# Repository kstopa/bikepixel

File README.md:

# Bike Pixels

Open Source Hardware project to build a set of highly customizable bycicle lights based on Arduino and Neo Pixel RGB matrixes. Currently all models can present different images in different colors with custom effects (blinking, bitting) and with adjustable brightness.

Check [Bike Pixel Official site](https://bikepixels.com) to the more details and recent news.

## Required software
All required applications to edit and design the different Bike Pixel models are open source. Bellow you can find all the tools that were used to design Bike Pixels:

* [Arduino IDE](https://www.arduino.cc/en/Main/Software): to write, biuld and upload the code to the Arduino board.
* [FreeCAD](https://www.freecadweb.org/wiki/Download): to design the cases.
* [KiCAD](http://kicad.org/download/): to design electronic schemas and the PCBs.
* [Fritzing](https://fritzing.org): only for circuit sketch documentation.

## Bike Pixel L (or rear)

This model it is intended to be installed in the back part of the bike like the saddle or over bike structure. Main properties and parts:

* Preset 10 diferent icons
* Adjustable color and brightness
* 64 LEDs NeoPixel matrix
* 84 x 84 x 14 mm (3.3 x 3.3 x 0.55 in)

### Components

To build your own Bike Pixel L you should have all the elements listed on this bill of materials:

* 1 x Arduino Pro Mini or Nano;
* 1 x NeoPixel 8x8 matrix (80x80x2mm);
* 3 x 10 kΩ resistence;
* 1 x 470 Ω resistence;
* 2 x 22 kΩ resistor;
* 1 x 1000 uf/6.3V capacitator (recommended but optional);
* 3 x vertical touch switches;
* 1 x on\off botton (optional if your battery holder have one built-in);
* 1 x TP4056 module;
* 1 x 5V Step-up module;
* 1 x >2000 mAh LiPo battery;
* 1 x M3 30mm bolt;
* 1 x M3 20mm bolt; 
* 2 x M3 nuts;
* connection PCB;
* wires and soldering stuff;
* 3D printed case;
* 3D printed holder.

More details on each part are commented on following points. Links to different proviedars and prices can be found on this blog entry.

### Case

The case is divided in multiple parts designed to be 3D printed. Current designs include body and holder models.

#### Main body

The body is composed the main body and a cover. You can print them using PLA altought for the cover a 1 mm thick piece of plexi is recommended.

You can get production files bellow.

| Part |                       Files                        |  
|------|----------------------------------------------------|
| Body | [sld](rear/case/body/case_bikepixels_rear.stl)     |
| Cover| [sld](rear/case/cover/case_bikepixels_rear_cover.stl), [svg](rear/case/cover/case_bikepixels_rear_cover.svg), [pdf](rear/case/cover/case_bikepixels_rear_cover.pdf) |

#### Bike attachment 

Current holder design is divided into two pieces. An attachment and a hook. To mount them on a bycicle you will need 2 x M3 nuts and 2 x M3 bolts of 30 and 20mm in lenght.

You can get production files bellow.

|  Part      |                           Files                             |
|------------|-------------------------------------------------------------|
| Hook       | [sld](rear/case/holder/holder_base_28mm-holder_hook.stl)    |
| Attachment | [sld](rear/case/holder/holder_base_28mm-holder_attach.stl)  |

### Electronics

#### Main components

To build your L model you will need all the electronic parts listed bellow along with some additional requirements.

|            Part              |              Comment                   |
|------------------------------|----------------------------------------|
| Arduino Nano or Pro Mini     | Clone or original                      |
| USB C TP4056 charging module | More information on [this blog entry](https://bikepixels.com/2019/11/10/how-to-add-a-lipo-battery-in-our-arduino-projects/)   |
| 5V Step-up module            | Any module designed for LiPo batteries |
| NeoPixel 8x8 RGB matrix      | Flexible 80x80x2mm model               |
| >2000 LiPo battery           | Max. 4 mm thicknes                     |

#### Conexions PCB

The PCB encapsulates the switches and manage connections between the Arduino board, the step-up module and the RGB matrix. All the design have been created with KiCAD. All the source files including schematinc, netlist and PCB board are availble [here](./rear/electronics/bikepixel rear/).

Production files are available in different formats and are linked bellow:

|                         Format                           |
|----------------------------------------------------------|
| [gerber](rear/electronics/production files/gerber)       |
| [pdf](rear/electronics/production files/pdf)             |
| [svg](rear/electronics/production files/svg)             |

#### Assambley

To connect evrything together please follow schema bellow. After soldering everthing you can proceed to upload the code to Arduino.

## Code 

To compile the BikePixel [code for Arduino](./rear/src/bikepixel_sketch.ino), you'll need some extra libraries:

* [Adafruit GFX](https://github.com/adafruit/Adafruit-GFX-Library)
* [Adafruit NeoPixel](https://github.com/adafruit/Adafruit_NeoPixel)
* [Adafruit NeoMatrix](https://github.com/adafruit/Adafruit_NeoMatrix)

Note that you can install these libraries directly from Arduino Studio (Sketch menu, > Include Library > Manage Libraries) or by placing it after download into the Arduino Library folder (usally in your home).

## Certification

Bike Pixel is certified by the Open Source Hardware Association ([OSHWA](https://oshwa.org)). 
OSWHA is a non-profit organization that advocates for open-source hardware focusing on promotion, education and commercialization of open 
products. OSHWA also manages certification program for open-source hardware that indicate that given product meet standard criteria for 
open-source compliance. Current Bike Pixel version has certificate number [PL000007](https://certification.oshwa.org/pl000007.html).

## License

As the project is compond by software, hardware and documentation each of these parts are licensed under the terms of specific license.

### Software License

Copyright © 2021 by BikePixels.com and contributors:

* Krzysztof Stopa ([kstopa](https://github.com/kstopa/)).

Bike Pixels contains free software: you can redistribute it and/or modify it under the terms of the GNU General Public License as published by the Free Software Foundation, either version 3 of the License, or any later version.

Bike Pixels is distributed in the hope that it will be useful, but WITHOUT ANY WARRANTY; without even the implied warranty of MERCHANTABILITY or FITNESS FOR A PARTICULAR PURPOSE. See the GNU Lesser General Public License for more details.

You should have received a copy of the GNU Lesser General Public License along with CAMS tools. If not, see http://www.gnu.org/licenses/.

### Hardware License

Copyright © 2021 by BikePixels.com and contributors:

* Krzysztof Stopa ([kstopa](https://github.com/kstopa/)).

Hardware elements is licensed under the CERN OHL v. 1.2.

You may redistribute and modify this documentation under the terms of the CERN OHL v.1.2. (http://ohwr.org/cernohl). This documentation is distributed WITHOUT ANY EXPRESS OR IMPLIED WARRANTY, INCLUDING OF MERCHANTABILITY, SATISFACTORY QUALITY AND FITNESS FOR A PARTICULAR PURPOSE. Please see the CERN OHL v.1.2 for applicable conditions.

### Documentation and images License

Copyright © 2021 by BikePixels.com and contributors:

* Krzysztof Stopa ([kstopa](https://github.com/kstopa/)).

Documentation and image files are distributed under the Attribution-NonCommercial-ShareAlike 4.0 International (CC BY-NC-SA 4.0) lisence. The full text of the license can be found at the [CC BY-NC-SA 4.0 page](https://creativecommons.org/licenses/by-nc-sa/4.0/legalcode).

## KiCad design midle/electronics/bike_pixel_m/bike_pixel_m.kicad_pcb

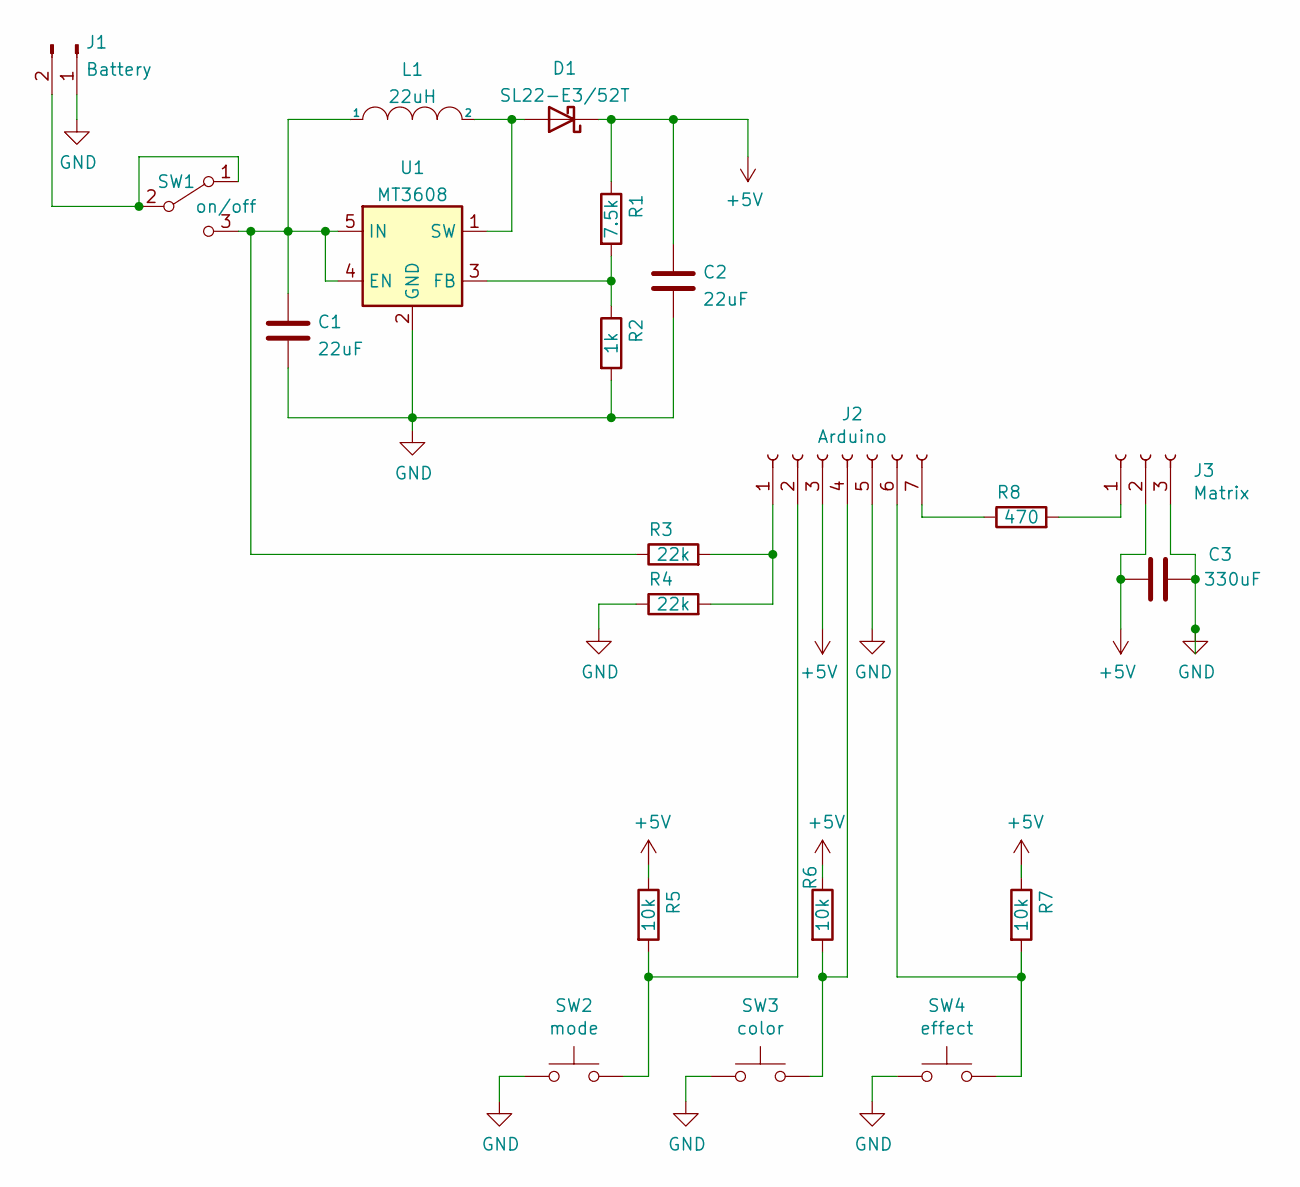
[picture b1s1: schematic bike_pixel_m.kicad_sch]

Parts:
C1, C2: 22uF; C_0805_2012Metric_Pad1.18x1.45mm_HandSolder
C3: 330uF; CP_Elec_8x6.2
D1: SL22-E3/52T; D_SMB_Handsoldering
J1: Battery; JST_XH_B2B-XH-AM_1x02_P2.50mm_Vertical
J2: Arduino; PinSocket_1x07_P2.54mm_Vertical
J3: Matrix; PinSocket_1x03_P2.54mm_Vertical
L1: 22uH; L_10.4x10.4_H4.8
R1: 7.5k; R_1210_3225Metric_Pad1.30x2.65mm_HandSolder
R2: 1k; R_1210_3225Metric_Pad1.30x2.65mm_HandSolder
R3, R4: 22k; R_1218_3246Metric_Pad1.22x4.75mm_HandSolder
R5, R6, R7: 10k; R_0603_1608Metric_Pad0.98x0.95mm_HandSolder
R8: 470; R_0603_1608Metric_Pad0.98x0.95mm_HandSolder
SW1: on/off; SW_SPDT_SS12D06_H5_SPACE_4.8
SW2: mode; SW_Tactile_SPST_Angled_PTS645Vx58-2LFS
SW3: color; SW_Tactile_SPST_Angled_PTS645Vx58-2LFS
SW4: effect; SW_Tactile_SPST_Angled_PTS645Vx58-2LFS
U1: MT3608; SOT-23-6

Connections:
+5V: C2.1, C3.2, D1.1 (K), J2.3, J3.2, R1.1, R5.1, R6.1, R7.1
GND: C1.2, C2.2, C3.1, J1.1, J2.5, J3.3, R2.2, R4.1, SW2.1, SW3.1, SW4.1, U1.2 (GND)
unnamed: C1.1, L1.1, R3.1, SW1.3 (C), U1.4 (EN), U1.5 (IN)
unnamed: D1.2 (A), L1.2, U1.1 (SW)
unnamed: J1.2, SW1.1 (A), SW1.2 (B)
unnamed: J2.1, R3.2, R4.2
unnamed: J2.2, R5.2, SW2.2
unnamed: J2.4, R6.2, SW3.2
unnamed: J2.6, R7.2, SW4.2
unnamed: J2.7, R8.1
unnamed: J3.1, R8.2
unnamed: R1.2, R2.1, U1.3 (FB)

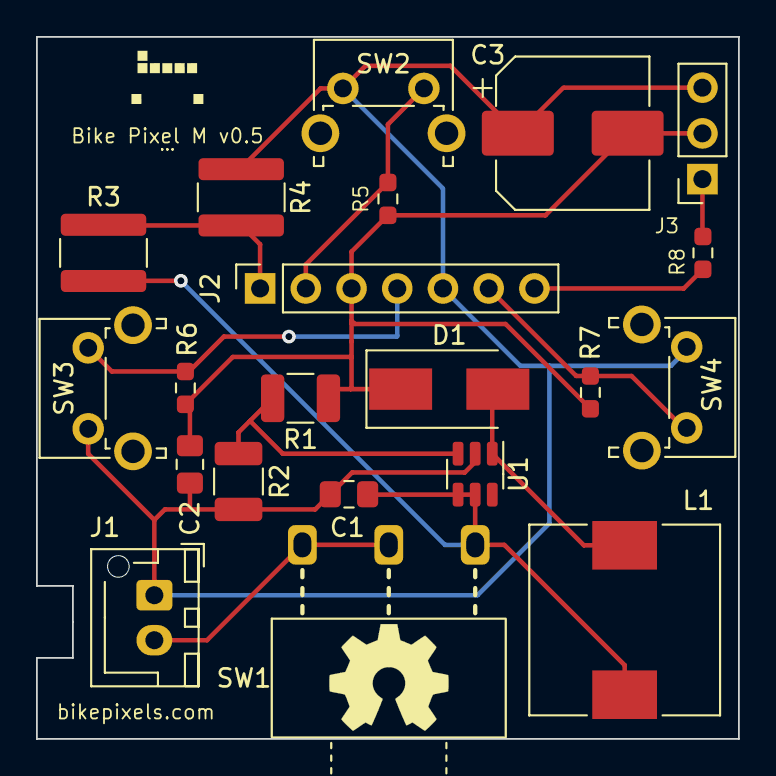
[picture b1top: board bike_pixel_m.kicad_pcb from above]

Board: 2 copper layers, 39.0 x 39.0 mm, 23 parts (0 on the bottom side), 12 nets.

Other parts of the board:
...: LOGO; Bike_Pixels_logo_solder
Bike Pixel M v0.5: LOGO; Bike_Pixels_logo_silk

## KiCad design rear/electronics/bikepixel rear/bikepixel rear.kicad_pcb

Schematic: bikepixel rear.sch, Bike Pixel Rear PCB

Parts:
C1: 470uF, 6.3V; C_Radial_D8.0mm_H7.0mm_P3.50mm
J1: Power; PinSocket_1x03_P2.54mm_Vertical
J2: Arduino; PinSocket_1x07_P2.54mm_Vertical
J3: Matrix; PinSocket_1x03_P2.54mm_Vertical
R1, R2: 22k; R_Axial_DIN0207_L6.3mm_D2.5mm_P7.62mm_Horizontal
R3, R4, R5: 10k; R_Axial_DIN0207_L6.3mm_D2.5mm_P7.62mm_Horizontal
R6: 470; R_Axial_DIN0207_L6.3mm_D2.5mm_P7.62mm_Horizontal
SW0: on/off; SW-SPDT-SS12D00-Angled
SW1: mode; SW_Tactile_SPST_Angled_PTS645Vx58-2LFS
SW2: color; SW_Tactile_SPST_Angled_PTS645Vx58-2LFS
SW3: effect; SW_Tactile_SPST_Angled_PTS645Vx58-2LFS

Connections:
+5V: C1.2, J2.3, J3.2, R3.1, R4.1, R5.1, SW0.3
GND: C1.1, J1.3, J2.5, J3.3, R1.1, SW1.1, SW2.1, SW3.1
unnamed: J1.1, R2.1
unnamed: J1.2, SW0.2
unnamed: J2.1, R1.2, R2.2
unnamed: J2.2, R3.2, SW1.2
unnamed: J2.4, R4.2, SW2.2
unnamed: J2.6, R5.2, SW3.2
unnamed: J2.7, R6.1
unnamed: J3.1, R6.2

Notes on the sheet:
Note that in the matrix specs a 1000 uF capacitator is recommended but due to size restrctions a smaller one is used.

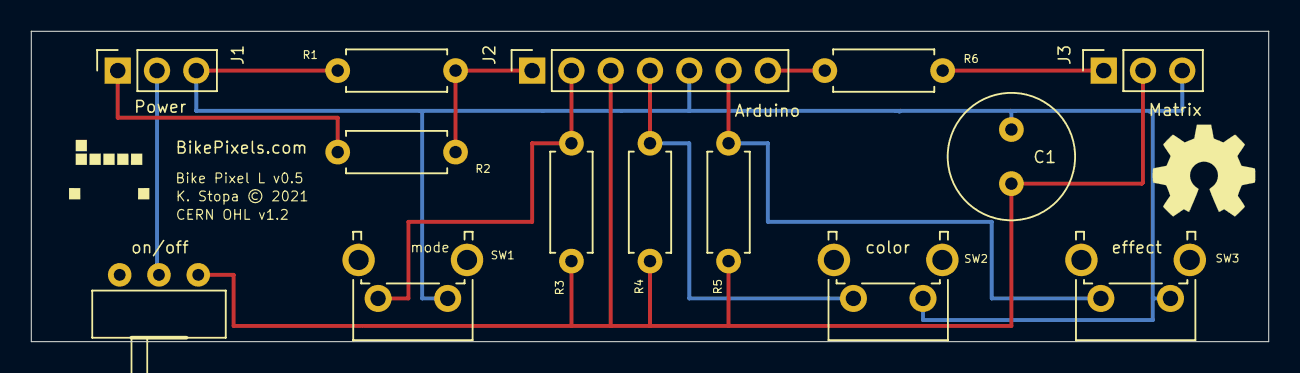
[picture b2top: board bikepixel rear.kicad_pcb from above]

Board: 2 copper layers, 80.0 x 20.1 mm, 17 parts (0 on the bottom side), 10 nets.

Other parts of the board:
CERN OHL v1.2: Bike Pixel L v0.5; bikepixels_logo_black_part_silk_05mm
K. Stopa © 2021: BikePixels.com; bikepixels_logo_red_part_solder_05mm
OSHW: OSHW; OSHW-Symbol_6.7x6mm_SilkScreen

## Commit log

2018-01-14 Added basic documentation and first version of the code with one simple effect.
2018-01-23 Added invader mode
2018-01-23 Added sketch
2018-01-23 Added sketch to documentation
2018-01-27 Improved protoboard schema, added PCB and production files. Written more documentation
2018-01-27 Added case image do readme
2018-01-28 Finished case design
2018-01-30 Added Christmas Tree mode
2018-01-30 Set PIN numbers according to schema
2018-02-05 Added skull mode
2018-02-15 Added dot and blinking dot modes
2018-06-18 New PCB with proper resistors
2018-07-01 Updated PCB design
2018-08-15 Improved protoboard. Added extra documentation
2018-09-03 New case design
2018-09-09 Updated case and documentation
2018-09-30 Improved documentation added optional middle part for the case
2018-09-30 Added heart icon and the capability to change the matrix birgthness by pressiong one of the buttons
2018-09-30 Update README.md
    Links
2018-10-11 Added birght setup
2019-09-21 First 3D printed case. Added Lisences
2019-09-24 Changed to CC BY SA license
2019-10-02 Enable color setup
2019-10-02 Added welcome screen
2019-11-20 Max brightness by default
2020-11-06 Separate between rear and front models
2020-11-10 Updated pcb design with battery connection and on button. Added basic battery checking into code. Added 3D printed basic case model
2021-01-24 Added new pcb design including power connections
2021-06-15 New rear PCB version. Added new PCB case
2021-06-15 Updated Licenses
2021-06-15 Updated design related files and documentation
2021-06-15 Added last BP front design (deprecated)
2021-06-15 Update all
2021-11-14 Added files for bike pixel rear with battery support and 3d printed case
2021-11-29 Added PCB design. Improved documentation
2021-11-29 Links on docs
2021-12-01 Added Bike Pixel L conection schema
2021-12-01 Front drafts
2021-12-01 Start with welcome mode
2021-12-13 Added OSHWA certification info
2022-01-11 Added new modes (Thunder, Warning, Ghost)
2022-01-11 Added Bike Pixel M PCB KiCad design with step-up IC and SMD parts
2022-01-15 Added Bike Pixel M PCB KiCad and production gerber files
2022-01-15 Improved documentation. Deleted KiCAD backup files
2022-11-11 Added Bike Pixels Middle (M) first case and final prototype PCB design
2022-11-11 Renamed to middle
2022-11-11 Added BP middle arduino sketch with 6 modes, color switching and 3 effects
2022-11-13 Added BP M cover design models

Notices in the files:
midle/electronics/bike_pixel_m/bike_pixel_m.kicad_pcb:
License: CERN OHL v1.2
rear/electronics/bikepixel rear/bikepixel rear.kicad_pcb:
License: CERN Open Hardware Licence v1.2
